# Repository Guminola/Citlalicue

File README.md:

# Citlalicue
Repositories of the Citlallicue mission

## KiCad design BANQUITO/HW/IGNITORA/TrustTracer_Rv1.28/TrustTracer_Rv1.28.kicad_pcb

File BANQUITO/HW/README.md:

# HARDWARE DE BANQUITO

Investigación y desarrollo de hardware para el banco de pruebas

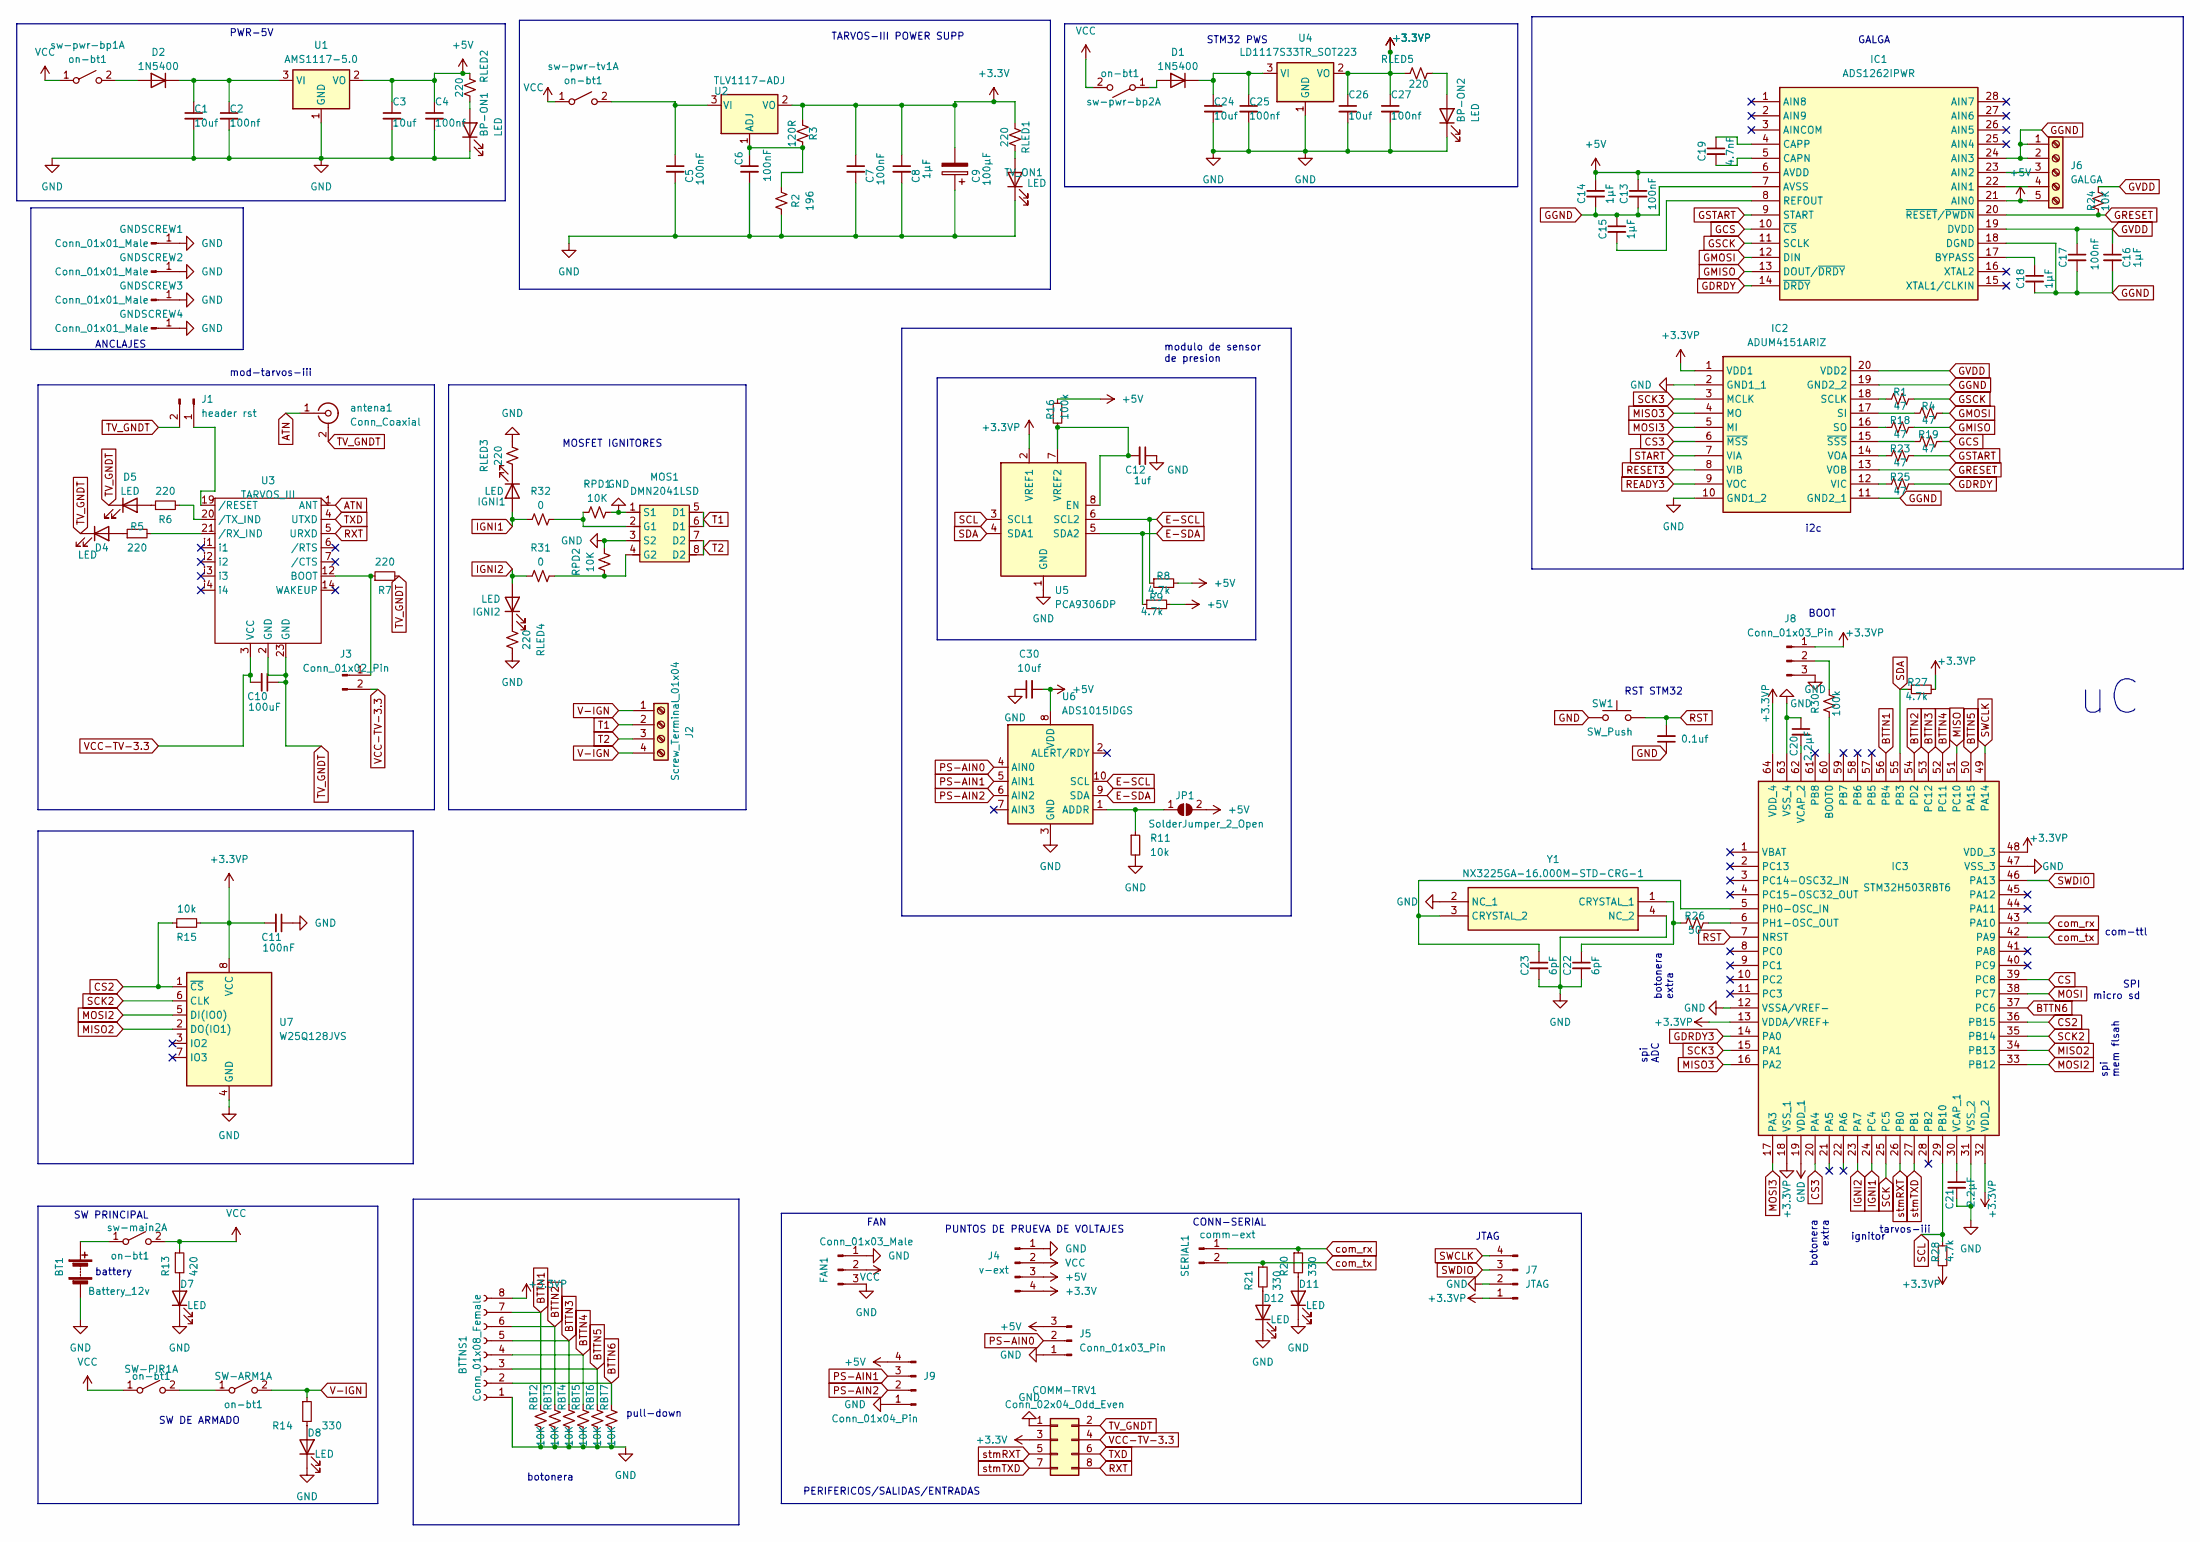
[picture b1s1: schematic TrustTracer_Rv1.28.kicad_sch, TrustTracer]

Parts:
BP-ON1, BP-ON2: LED; LED_0805_2012Metric
BT1: Battery_12v; AMASS_XT30UPB-M_1x02_P5.0mm_Vertical
BTTNS1: Conn_01x08_Female; JST_EH_B8B-EH-A_1x08_P2.50mm_Vertical
C1, C3, C24, C26, C30: 10uf; C_0805_2012Metric_Pad1.18x1.45mm_HandSolder
C2, C4, C25, C27: 100nf; C_0805_2012Metric_Pad1.18x1.45mm_HandSolder
C5, C6, C7, C11, C13, C17: 100nF; C_0805_2012Metric_Pad1.18x1.45mm_HandSolder
C8, C14, C15, C16, C18: 1μF; C_0805_2012Metric_Pad1.18x1.45mm_HandSolder
C9: 100μF; CP_EIA-2012-12_Kemet-R
C10: 100uF; C_0805_2012Metric_Pad1.18x1.45mm_HandSolder
C12: 1uf; C_0805_2012Metric_Pad1.18x1.45mm_HandSolder
C19: 4.7nF; C_0805_2012Metric_Pad1.18x1.45mm_HandSolder
C20, C21: 2.2μF; C_0805_2012Metric_Pad1.18x1.45mm_HandSolder
C22, C23: 6pF; C_0805_2012Metric_Pad1.18x1.45mm_HandSolder
C28: 0.1uf; C_0805_2012Metric_Pad1.18x1.45mm_HandSolder
COMM-TRV1: Conn_02x04_Odd_Even; PinHeader_2x04_P2.00mm_Vertical
D1, D2: 1N5400; D_SOD-123F
D4, D5, D7, D8, D11, D12: LED; LED_0805_2012Metric
FAN1: Conn_01x03_Male; PinHeader_1x03_P2.54mm_Vertical
GNDSCREW1, GNDSCREW2, GNDSCREW3, GNDSCREW4: Conn_01x01_Male; MountingHole_2.2mm_M2_Pad_Via
IC1: ADS1262IPWR; ADS1263IPWR; Manufacturer_Part_Number ADS1262IPWR; Mouser Part Number 595-ADS1262IPWR
IC2: ADUM4151ARIZ; Manufacturer_Part_Number ADUM4151ARIZ; Mouser Part Number 584-ADUM4151ARIZ
IC3: STM32H503RBT6; Manufacturer_Part_Number STM32H503RBT6
IGNI1, IGNI2: LED; LED_0805_2012Metric
J1: header rst; PinHeader_1x02_P2.54mm_Vertical
J2: Screw_Terminal_01x04; TerminalBlock_Phoenix_PT-1,5-4-5.0-H_1x04_P5.00mm_Horizontal
J3: Conn_01x02_Pin; PinHeader_1x02_P2.54mm_Vertical
J4: v-ext; PinHeader_1x04_P2.54mm_Vertical
J5: Conn_01x03_Pin; TerminalBlock_Phoenix_PT-1,5-3-3.5-H_1x03_P3.50mm_Horizontal
J6: GALGA; TerminalBlock_Phoenix_PT-1,5-5-3.5-H_1x05_P3.50mm_Horizontal
J7: JTAG; PinHeader_1x04_P2.54mm_Vertical
J8: Conn_01x03_Pin; PinHeader_1x03_P2.54mm_Vertical
J9: Conn_01x04_Pin; PinHeader_1x04_P2.54mm_Vertical
JP1: SolderJumper_2_Open; SolderJumper-2_P1.3mm_Open_RoundedPad1.0x1.5mm
MOS1: DMN2041LSD; SOIC127P600X175-8M
R1, R4, R18, R19, R23, R25: 47; R_0805_2012Metric_Pad1.20x1.40mm_HandSolder
R2: 196; R_0805_2012Metric_Pad1.20x1.40mm_HandSolder
R3: 120R; R_0805_2012Metric_Pad1.20x1.40mm_HandSolder
R5, R6, R7: 220; R_0805_2012Metric_Pad1.20x1.40mm_HandSolder
R8, R9, R27, R28: 4.7k; R_0805_2012Metric_Pad1.20x1.40mm_HandSolder
R11, R15: 10k; R_0805_2012Metric_Pad1.20x1.40mm_HandSolder
R13: 420; R_0805_2012Metric_Pad1.20x1.40mm_HandSolder
R14, R20, R21: 330; R_0805_2012Metric_Pad1.20x1.40mm_HandSolder
R16, R30: 100k; R_0805_2012Metric_Pad1.20x1.40mm_HandSolder
R24: 10K; R_0805_2012Metric_Pad1.20x1.40mm_HandSolder
R26: 50; R_0805_2012Metric_Pad1.20x1.40mm_HandSolder
R31, R32: 0; R_0805_2012Metric_Pad1.20x1.40mm_HandSolder
RBT2, RBT3, RBT4, RBT5, RBT6, RBT7: 10K; R_0805_2012Metric_Pad1.20x1.40mm_HandSolder
RLED1, RLED2, RLED3, RLED4, RLED5: 220; R_0805_2012Metric_Pad1.20x1.40mm_HandSolder
RPD1, RPD2: 10K; R_0805_2012Metric_Pad1.20x1.40mm_HandSolder
SERIAL1: comm-ext; PinHeader_1x02_P2.54mm_Vertical
SW1: SW_Push; SW_SPST_TL3342
SW-ARM1: on-bt1; TerminalBlock_Phoenix_PT-1,5-2-3.5-H_1x02_P3.50mm_Horizontal
SW-PIR1: on-bt1; TerminalBlock_Phoenix_PT-1,5-2-3.5-H_1x02_P3.50mm_Horizontal
TV_ON1: LED; LED_0805_2012Metric
U1: AMS1117-5.0; SOT-223-3_TabPin2
U2: TLV1117-ADJ; SOT-223
U3: TARVOS_III; tarvos-iii
U4: LD1117S33TR_SOT223; SOT-223-3_TabPin2
U5: PCA9306DP; TSSOP-8_3x3mm_P0.65mm
U6: ADS1015IDGS; TSSOP-10_3x3mm_P0.5mm
U7: W25Q128JVS; SOIC127P600X175-8M
Y1: NX3225GA-16.000M-STD-CRG-1; NX3225GA16000MSTDCRG1; Mouser Part Number 344-NX3225GA16MSTRG1
antena1: Conn_Coaxial; SMA_Wurth_60312002114503_Vertical
sw-main2: on-bt1; TerminalBlock_Phoenix_PT-1,5-2-3.5-H_1x02_P3.50mm_Horizontal
sw-pwr-bp1, sw-pwr-bp2: on-bt1; TerminalBlock_Phoenix_PT-1,5-2-3.5-H_1x02_P3.50mm_Horizontal
sw-pwr-tv1: on-bt1; TerminalBlock_Phoenix_PT-1,5-2-3.5-H_1x02_P3.50mm_Horizontal

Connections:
+3.3V: C7.1, C8.1, C9.2, COMM-TRV1.3, J4.4, R3.2, RLED1.2, U2.2 (VO)
+3.3VP: BTTNS1.8, C11.2, C26.1, C27.1, IC2.1 (VDD1), IC3.13 (VDDA/VREF+), IC3.19 (VDD_1), IC3.32 (VDD_2), IC3.48 (VDD_3), IC3.64 (VDD_4), J7.1, J8.1, R15.2, R27.2, R28.2, RLED5.2, U4.2 (VO), U5.2 (VREF1), U7.8 (VCC)
+5V: C3.1, C4.1, C13.1, C14.1, C30.2, IC1.6 (AVDD), IC1.21 (AIN0), J4.3, J5.3, J6.5, J9.4, JP1.2 (B), R8.2, R9.2, R16.1, RLED2.2, U1.2 (VO), U6.8 (VDD)
ATN: U3.1 (ANT), antena1.1 (In)
BTTN1: BTTNS1.7, IC3.56 (PB4), RBT2.1
BTTN2: BTTNS1.6, IC3.54 (PD2), RBT3.1
BTTN3: BTTNS1.5, IC3.53 (PC12), RBT4.1
BTTN4: BTTNS1.4, IC3.52 (PC11), RBT5.1
BTTN5: BTTNS1.3, IC3.50 (PA15), RBT6.1
BTTN6: BTTNS1.2, IC3.37 (PC6), RBT7.1
CS: IC3.39 (PC8)
CS2: IC3.36 (PB15), R15.1, U7.1 (~CS)
CS3: IC2.6 (~MSS), IC3.20 (PA4)
E-SCL: R8.1, U5.6 (SCL2), U6.10 (SCL)
E-SDA: R9.1, U5.5 (SDA2), U6.9 (SDA)
GCS: IC1.10 (~CS), R19.2
GDRDY: IC1.14 (~DRDY), R25.2
GDRDY3: IC3.14 (PA0)
GGND: C13.2, C14.2, C15.1, C16.2, C17.2, C18.2, IC1.7 (AVSS), IC1.18 (DGND), IC1.24 (AIN3), IC2.11 (GND2_1), IC2.19 (GND2_2), J6.1, J6.2
GMISO: IC1.13 (DOUT/~DRDY), R18.2
GMOSI: IC1.12 (DIN), R4.2
GND: BP-ON1.1 (K), BP-ON2.1 (K), BT1.2 (-), BTTNS1.1, C1.2, C2.2, C3.2, C4.2, C5.2, C6.2, C7.2, C8.2, C9.1, C11.1, C12.1, C20.1, C21.2, C22.2, C23.2, C24.2, C25.2, C26.2, C27.2, C28.1, C30.1, COMM-TRV1.1, D7.1 (K), D8.1 (K), D11.1 (K), D12.1 (K), FAN1.1, FAN1.3, GNDSCREW1.1, GNDSCREW2.1, GNDSCREW3.1, GNDSCREW4.1, IC2.2 (GND1_1), IC2.10 (GND1_2), IC3.12 (VSSA/VREF-), IC3.18 (VSS_1), IC3.31 (VSS_2), IC3.47 (VSS_3), IC3.63 (VSS_4), J4.1, J5.1, J7.2, J8.3, J9.1, MOS1.1 (S1), MOS1.3 (S2), R2.1, R11.2, RBT2.2, RBT3.2, RBT4.2, RBT5.2, RBT6.2, RBT7.2, RLED3.2, RLED4.2, RPD1.2, RPD2.2, SW1.1, TV_ON1.1 (K), U1.1 (GND), U4.1 (GND), U5.1 (GND), U6.3 (GND), U7.4 (GND), Y1.2 (NC_1), Y1.4 (NC_2)
GRESET: IC1.20 (~RESET/~PWDN), IC2.13 (VOB), R24.1
GSCK: IC1.11 (SCLK), R1.2
GSTART: IC1.9 (START), R23.2
GVDD: C16.1, C17.1, IC1.19 (DVDD), IC2.20 (VDD2), R24.2
IGNI1: IC3.24 (PC4), IGNI1.2 (A), R32.1
IGNI2: IC3.23 (PA7), IGNI2.2 (A), R31.1
MISO: IC3.51 (PC10)
MISO2: IC3.34 (PB13), U7.2 (DO(IO1))
MISO3: IC2.4 (MO), IC3.16 (PA2)
MOSI: IC3.38 (PC7)
MOSI2: IC3.33 (PB12), U7.5 (DI(IO0))
MOSI3: IC2.5 (MI), IC3.17 (PA3)
unnamed: BP-ON1.2 (A), RLED2.1
unnamed: BP-ON2.2 (A), RLED5.1
unnamed: BT1.1 (+), sw-main2.1 (A)
unnamed: D1.2 (A), sw-pwr-bp2.1 (A)
unnamed: C24.1, C25.1, D1.1 (K), U4.3 (VI)
unnamed: D2.2 (A), sw-pwr-bp1.2 (B)
unnamed: C1.1, C2.1, D2.1 (K), U1.3 (VI)
unnamed: D4.2 (A), R5.1
unnamed: D5.2 (A), R6.1
unnamed: D7.2 (A), R13.2
unnamed: D8.2 (A), R14.2
unnamed: D11.2 (A), R20.2
unnamed: D12.2 (A), R21.2
unnamed: IC1.22 (AIN1), J6.4
unnamed: IC1.23 (AIN2), J6.3
unnamed: C18.1, IC1.17 (BYPASS)
unnamed: C19.2, IC1.5 (CAPN)
unnamed: C19.1, IC1.4 (CAPP)
unnamed: C15.2, IC1.8 (REFOUT)
unnamed: IC2.18 (SCLK), R1.1
unnamed: IC2.17 (SI), R4.1
unnamed: IC2.16 (SO), R18.1
unnamed: IC2.12 (VIC), R25.1
unnamed: IC2.14 (VOA), R23.1
unnamed: IC2.15 (~SSS), R19.1
unnamed: IC3.60 (BOOT0), R30.1
unnamed: C23.1, IC3.5 (PH0-OSC_IN), Y1.3 (CRYSTAL_2)
unnamed: IC3.6 (PH1-OSC_OUT), R26.2
unnamed: C21.1, IC3.30 (VCAP_1)
unnamed: C20.2, IC3.62 (VCAP_2)
unnamed: IGNI1.1 (K), RLED3.1
unnamed: IGNI2.1 (K), RLED4.1
unnamed: J1.1, U3.19 (/RESET)
unnamed: J3.1, R7.1, U3.12 (BOOT)
unnamed: J8.2, R30.2
unnamed: JP1.1 (A), R11.1, U6.1 (ADDR)
unnamed: MOS1.2 (G1), R32.2, RPD1.1
unnamed: MOS1.4 (G2), R31.2, RPD2.1
unnamed: SW-ARM1.1 (A), SW-PIR1.2 (B)
unnamed: RLED1.1, TV_ON1.2 (A)
unnamed: C6.1, R2.2, R3.1, U2.1 (ADJ)
unnamed: C5.1, U2.3 (VI), sw-pwr-tv1.2 (B)
unnamed: R5.2, U3.21 (/RX_IND)
unnamed: R6.2, U3.20 (/TX_IND)
unnamed: C12.2, R16.2, U5.7 (VREF2), U5.8 (EN)
unnamed: C22.1, R26.1, Y1.1 (CRYSTAL_1)
PS-AIN0: J5.2, U6.4 (AIN0)
PS-AIN1: J9.3, U6.5 (AIN1)
PS-AIN2: J9.2, U6.6 (AIN2)
READY3: IC2.9 (VOC)
RESET3: IC2.8 (VIB)
RST: C28.2, IC3.7 (NRST), SW1.2
RXT: COMM-TRV1.8, U3.5 (URXD)
SCK: IC3.25 (PC5)
SCK2: IC3.35 (PB14), U7.6 (CLK)
SCK3: IC2.3 (MCLK), IC3.15 (PA1)
SCL: IC3.29 (PB10), R28.1, U5.3 (SCL1)
SDA: IC3.55 (PB3), R27.1, U5.4 (SDA1)
START: IC2.7 (VIA)
SWCLK: IC3.49 (PA14), J7.4
SWDIO: IC3.46 (PA13), J7.3
T1: J2.2, MOS1.5 (D1), MOS1.6 (D1)
T2: J2.3, MOS1.7 (D2), MOS1.8 (D2)
TV_GNDT: C10.1, COMM-TRV1.2, D4.1 (K), D5.1 (K), J1.2, R7.2, U3.2 (GND), U3.23 (GND), antena1.2 (Ext)
TXD: COMM-TRV1.6, U3.4 (UTXD)
V-IGN: J2.1, J2.4, R14.1, SW-ARM1.2 (B)
VCC: FAN1.2, J4.2, R13.1, SW-PIR1.1 (A), sw-main2.2 (B), sw-pwr-bp1.1 (A), sw-pwr-bp2.2 (B), sw-pwr-tv1.1 (A)
VCC-TV-3.3: C10.2, COMM-TRV1.4, J3.2, U3.3 (VCC)
com_rx: IC3.43 (PA10), R20.1, SERIAL1.1
com_tx: IC3.42 (PA9), R21.1, SERIAL1.2
stmRXT: COMM-TRV1.5, IC3.26 (PB0)
stmTXD: COMM-TRV1.7, IC3.27 (PB1)

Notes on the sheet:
JTAG
ignitor
PERIFERICOS/SALIDAS/ENTRADAS
mod-tarvos-iii
PUNTOS DE PRUEVA DE VOLTAJES
battery
BOOT
ANCLAJES
botonera
TARVOS-III POWER SUPP
FAN
SW PRINCIPAL
spi ADC
SW DE ARMADO
botonera extra
PWR-5V
GALGA
i2c
com-ttl
pull-down
tarvos-iii
MOSFET IGNITORES
STM32 PWS
SPI micro sd
modulo de sensor de presion
CONN-SERIAL
RST STM32
spi mem flsah

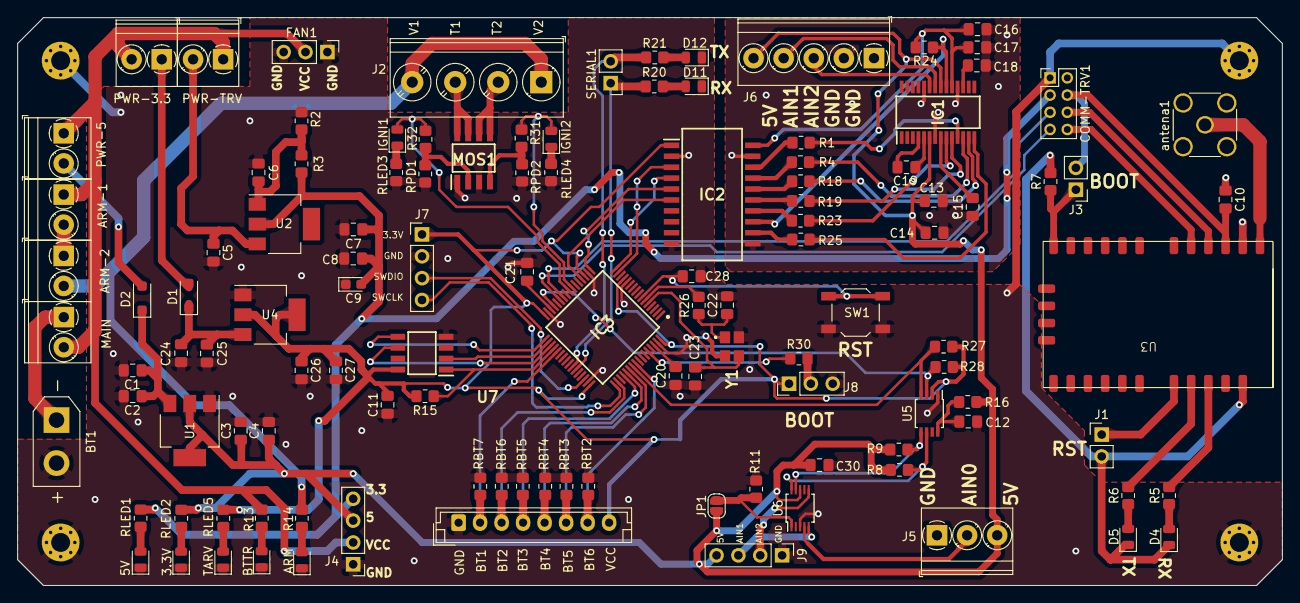
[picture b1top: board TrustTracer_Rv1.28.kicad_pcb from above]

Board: 2 copper layers, 147.0 x 66.0 mm, 122 parts (1 on the bottom side), 98 nets.

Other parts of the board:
G2: LOGO; SPACE

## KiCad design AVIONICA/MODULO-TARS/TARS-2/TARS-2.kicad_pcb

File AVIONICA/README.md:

# AVIONICA PARA LA MISION

T.A.R.S

Telemetry, Avionics,Recovery,System

sistema de avionica y sus diferentes modulos de la mision

1/3 modulo gps  Erinome-1

2/3 modulo de comunicaciones Tarvos-iii

3/3 avionica STM-32

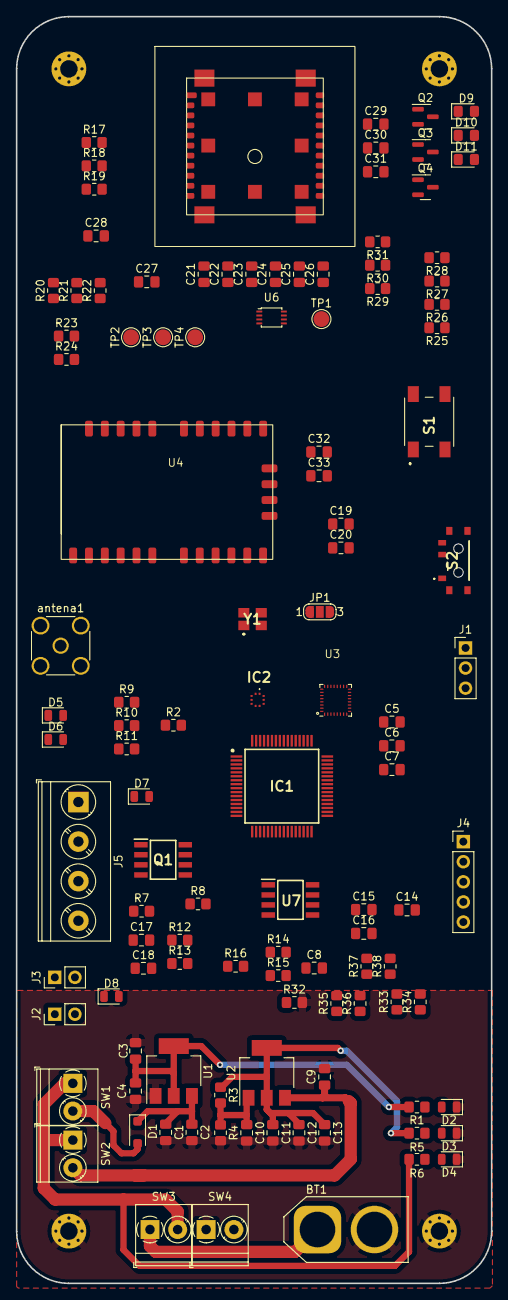
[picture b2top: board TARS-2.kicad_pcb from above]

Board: 2 copper layers, 60.0 x 160.0 mm, 118 parts (0 on the bottom side), 70 nets.

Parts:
BT1: Battery; AMASS_XT60-M_1x02_P7.20mm_Vertical
C1, C3: 10uf; C_0805_2012Metric_Pad1.18x1.45mm_HandSolder
C2, C4, C9, C10, C11, C18, C19, C27, C28: 100nf; C_0805_2012Metric_Pad1.18x1.45mm_HandSolder
C5, C6, C7, C8: 6pf; C_0805_2012Metric_Pad1.18x1.45mm_HandSolder
C12, C32: 1uf; C_0805_2012Metric_Pad1.18x1.45mm_HandSolder
C13: 100uf; C_0805_2012Metric_Pad1.18x1.45mm_HandSolder
C14: C_Small; C_0805_2012Metric_Pad1.18x1.45mm_HandSolder
C15: .1uf; C_0805_2012Metric_Pad1.18x1.45mm_HandSolder
C16, C17: .1f; C_0805_2012Metric_Pad1.18x1.45mm_HandSolder
C20: 100uF; C_0805_2012Metric_Pad1.18x1.45mm_HandSolder
C21, C23, C29, C30, C31: 100pf; C_0805_2012Metric_Pad1.18x1.45mm_HandSolder
C22, C24: 4.7uf; C_0805_2012Metric_Pad1.18x1.45mm_HandSolder
C25, C26: 18pf; C_0805_2012Metric_Pad1.18x1.45mm_HandSolder
C33: 100nF; C_0805_2012Metric_Pad1.18x1.45mm_HandSolder
D1: 1N5400; D_SOD-123F
D2, D7, D8: LED; LED_0805_2012Metric
D3, D4, D5, D6: LED_Small; LED_0805_2012Metric
D9, D10, D11: LED_Small; LED_0805_2012Metric_Pad1.15x1.40mm_HandSolder
GNDSCREW1, GNDSCREW2, GNDSCREW3, GNDSCREW4: Conn_01x01_Male; MountingHole_2.2mm_M2_Pad_Via
IC1: STM32H503RBT6
IC2: BMP390
J1: Conn_01x03_Pin; PinHeader_1x03_P2.54mm_Vertical
J2: header rst; PinHeader_1x02_P2.54mm_Vertical
J3: Conn_01x02_Pin; PinHeader_1x02_P2.54mm_Vertical
J4: Conn_01x05_Pin; PinHeader_1x05_P2.54mm_Vertical
J5: Screw_Terminal_01x04; TerminalBlock_Phoenix_PT-1,5-4-5.0-H_1x04_P5.00mm_Horizontal
JP1: Jumper_3_Open; SolderJumper-3_P1.3mm_Open_RoundedPad1.0x1.5mm_NumberLabels
Q1: DMN2041LSD-13; SOIC127P600X175-8M
Q2, Q3, Q4: BSS138; SOT-23
R1, R5, R12, R13, R14, R15, R16: 220; R_0805_2012Metric_Pad1.20x1.40mm_HandSolder
R2: 50; R_0805_2012Metric_Pad1.20x1.40mm_HandSolder
R3: 120; R_0805_2012Metric_Pad1.20x1.40mm_HandSolder
R4: 196; R_0805_2012Metric_Pad1.20x1.40mm_HandSolder
R6: 420; R_0805_2012Metric_Pad1.20x1.40mm_HandSolder
R7, R24, R28, R29: 100k; R_0805_2012Metric_Pad1.20x1.40mm_HandSolder
R8, R9, R19, R23, R26, R27, R32, R33, R38: 10k; R_0805_2012Metric_Pad1.20x1.40mm_HandSolder
R10, R11, R20: 0; R_0805_2012Metric_Pad1.20x1.40mm_HandSolder
R17, R18: 100; R_0805_2012Metric_Pad1.20x1.40mm_HandSolder
R21: 1.8k; R_0805_2012Metric_Pad1.20x1.40mm_HandSolder
R22: 1.5k; R_0805_2012Metric_Pad1.20x1.40mm_HandSolder
R25, R31: 2.2k; R_0805_2012Metric_Pad1.20x1.40mm_HandSolder
R30: 1k; R_0805_2012Metric_Pad1.20x1.40mm_HandSolder
R34, R35, R36, R37: 330; R_0805_2012Metric_Pad1.20x1.40mm_HandSolder
S1: PSB-WURT
S2: SW-WURT
SW1, SW3: MAIN; TerminalBlock_Phoenix_PT-1,5-2-3.5-H_1x02_P3.50mm_Horizontal
SW2: TRV-PWR; TerminalBlock_Phoenix_PT-1,5-2-3.5-H_1x02_P3.50mm_Horizontal
SW4: RST; TerminalBlock_Phoenix_PT-1,5-2-3.5-H_1x02_P3.50mm_Horizontal
TP1: CTS; TestPoint_Pad_D2.0mm
TP2: GND; TestPoint_Pad_D2.0mm
TP3: 1v8; TestPoint_Pad_D2.0mm
TP4: RTS; TestPoint_Pad_D2.0mm
U1: LD1117S33TR_SOT223; SOT-223-3_TabPin2
U2: TLV1117-ADJ; SOT-223-3_TabPin2
U3: ICM-30670
U4: TARVOS_III; tarvos-iii
U5: ERINOME-l; Erinome-l
U6: TXB0102DCU; VSSOP-8_2.4x2.1mm_P0.5mm
U7: W25Q128JVS; SOIC127P600X175-8M
Y1: NX3225GA-16.000M-STD-CRG-1; NX3225GA16000MSTDCRG1
antena1: Conn_Coaxial; SMA_Wurth_60312002114503_Vertical

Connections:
1pps: R26.1, U5.21 (1PPS)
3v3-ldo: C23.1, C24.1, U5.3 (V_BACKUP)
+1V8: R20.1, TP3.1, U5.9 (1V8)
+3.3V: C11.1, C12.1, C13.1, C21.1, C22.1, C28.1, D9.2 (A), D10.2 (A), D11.2 (A), R3.1, R5.1, R19.2, R22.2, S2.1, U2.2 (VO), U5.8 (VCC), U6.7 (VCCB)
+12V: R6.1, SW1.1 (A), SW2.1 (A), SW3.2 (B)
ATN: U4.1 (ANT), antena1.1 (In)
CS2: R38.1, U7.1 (~CS)
GND: BT1.2 (-), C1.2, C2.2, C3.2, C4.2, C5.2, C6.2, C7.1, C8.2, C9.2, C10.2, C11.2, C12.2, C13.2, C14.2, C15.1, C16.1, C17.1, C18.2, C19.2, C21.2, C22.2, C23.2, C24.2, C25.1, C26.1, C27.2, C28.2, C29.2, C30.2, C31.2, C32.2, C33.1, D2.1 (K), D3.1 (K), D4.1 (K), GNDSCREW1.1, GNDSCREW2.1, GNDSCREW3.1, GNDSCREW4.1, IC1.12 (VSSA/VREF-), IC1.18 (VSS_1), IC1.31 (VSS_2), IC1.47 (VSS_3), IC1.63 (VSS_4), IC2.3 (VSS_1), IC2.8 (VSS_2), IC2.9 (VSS_3), J1.3, J4.5, JP1.1 (A), Q1.1 (S1), Q1.3 (S2), Q2.2 (S), Q3.2 (S), Q4.2 (S), R4.2, R8.2, R9.2, R12.1, R13.2, R21.2, R24.2, R28.2, R29.2, R32.2, S2.3, SW4.1, TP2.1, U1.1 (GND), U3.1 (VDDIO), U3.14 (GND), U5.10 (GND), U5.11 (GND), U5.12 (GND), U6.2 (GND), U7.4 (GND), Y1.2 (NC_1), Y1.4 (NC_2)
IGN1: D5.2 (A), R10.1
IGN2: D6.2 (A), R11.1
unnamed: BT1.1 (+), SW3.1 (A)
unnamed: D1.2 (A), SW1.2 (B)
unnamed: C1.1, C2.1, D1.1 (K), U1.3 (VI)
unnamed: D2.2 (A), R1.1
unnamed: D3.2 (A), R5.2
unnamed: D4.2 (A), R6.2
unnamed: D5.1 (K), R12.2
unnamed: D6.1 (K), R13.1
unnamed: D7.2 (A), R14.1
unnamed: D8.2 (A), R15.1
unnamed: D9.1 (K), R25.1
unnamed: D10.1 (K), R30.1
unnamed: D11.1 (K), R31.1
unnamed: IC1.60 (BOOT0), R7.2
unnamed: C5.1, IC1.5 (PH0-OSC_IN), Y1.3 (CRYSTAL_2)
unnamed: IC1.6 (PH1-OSC_OUT), R2.2
unnamed: C8.1, IC1.30 (VCAP_1)
unnamed: C7.2, IC1.62 (VCAP_2)
unnamed: IC2.5 (SDO), JP1.2 (C)
unnamed: J1.2, R7.1
unnamed: J2.1, U4.19 (/RESET)
unnamed: J3.1, R16.1, U4.12 (BOOT)
unnamed: J4.1, R34.2
unnamed: J4.2, R35.2
unnamed: J4.3, R36.2
unnamed: J4.4, R37.2
unnamed: Q1.2 (G1), R8.1, R10.2
unnamed: Q1.4 (G2), R9.1, R11.2
unnamed: Q2.3 (D), R25.2
unnamed: C29.1, Q2.1 (G), R23.2, R24.1
unnamed: Q3.3 (D), R30.2
unnamed: C30.1, Q3.1 (G), R26.2, R28.1
unnamed: Q4.3 (D), R31.2
unnamed: C31.1, Q4.1 (G), R27.2, R29.1
unnamed: R33.1, S2.2
unnamed: R32.1, S1.1 (NO_1), S1.2 (NO_2)
unnamed: C9.1, SW2.2 (B), U2.3 (VI)
unnamed: C10.1, R3.2, R4.1, U2.1 (ADJ)
unnamed: C16.2, U3.11 (REGOUT)
unnamed: R14.2, U4.21 (/RX_IND)
unnamed: R15.2, U4.20 (/TX_IND)
unnamed: C25.2, R17.2, U5.1 (RX)
unnamed: C26.2, R18.2, U5.2 (TX)
unnamed: TP1.1, U5.4 (/CTS)
unnamed: TP4.1, U6.8 (B1)
unnamed: C6.1, R2.1, Y1.1 (CRYSTAL_1)
ON-OFF: R33.2, U5.17 (ON_OF)
RST: C14.1, C32.1, S1.3 (COM_1), S1.4 (COM_2), SW4.2, U5.16 (/RST)
RTS-1V8: U5.5 (/RTS), U6.5 (A1)
SCL: IC2.2 (SCK), U3.10 (SCLK/SCL)
SDA: IC2.4 (SDI), U3.9 (SDI/SDA)
T1: J5.2, Q1.7 (D1_1), Q1.8 (D1_2)
T2: J5.3, Q1.5 (D2_1), Q1.6 (D2_2)
TV_GNDT: C20.1, D7.1 (K), D8.1 (K), J2.2, R16.2, U4.2 (GND), U4.23 (GND), antena1.2 (Ext)
TX-GNSS-1V8: R18.1, R27.1, U6.4 (A2)
V-IGN: J5.1, J5.4
VCC-TV-3.3: C20.2, J3.2, U4.3 (VCC)
VCCA: C27.1, R20.2, R21.1, R22.1, U6.3 (VCCA), U6.6 (OE)
VDDIO: C3.1, C4.1, C15.2, C17.2, C18.1, C19.1, C33.2, IC1.13 (VDDA/VREF+), IC1.19 (VDD_1), IC1.32 (VDD_2), IC1.48 (VDD_3), IC1.64 (VDD_4), IC2.1 (VDDIO), IC2.10 (VDD), J1.1, JP1.3 (B), R1.2, R38.2, U1.2 (VO), U3.12 (VDD), U7.8 (VCC)
wkp: R23.1, U5.15 (WAKE-UP)

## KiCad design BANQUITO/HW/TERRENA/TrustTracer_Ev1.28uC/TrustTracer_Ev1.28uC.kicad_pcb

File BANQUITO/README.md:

# Banco-de-Pruebas

Investigación y desarrollo de hardware y software para el banco de pruebas

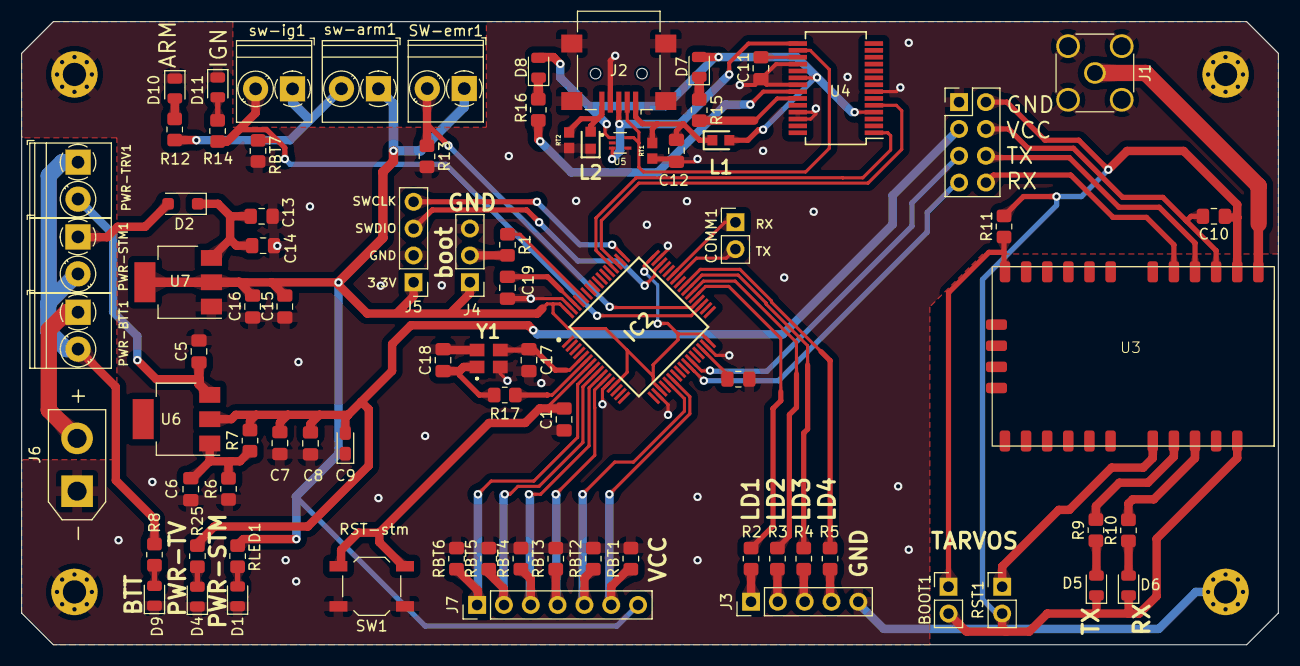
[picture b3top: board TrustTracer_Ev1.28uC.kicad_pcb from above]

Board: 2 copper layers, 119.0 x 59.0 mm, 87 parts (1 on the bottom side), 68 nets.

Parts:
BOOT1: Conn_01x02_Pin; PinHeader_1x02_P2.54mm_Vertical
C1: 0.1uf; C_0805_2012Metric_Pad1.18x1.45mm_HandSolder
C5, C6, C7, C11: 100nF; C_0805_2012Metric_Pad1.18x1.45mm_HandSolder
C8: 1μF; C_0805_2012Metric_Pad1.18x1.45mm_HandSolder
C9: 100μF; CP_EIA-2012-15_AVX-P_Pad1.30x1.05mm_HandSolder
C10: 100uF; C_0805_2012Metric_Pad1.18x1.45mm_HandSolder
C12: 10nF; C_0805_2012Metric_Pad1.18x1.45mm_HandSolder
C13, C15: 10uf; C_0805_2012Metric_Pad1.18x1.45mm_HandSolder
C14, C16: 100nf; C_0805_2012Metric_Pad1.18x1.45mm_HandSolder
C17, C18: 6pF; C_0805_2012Metric_Pad1.18x1.45mm_HandSolder
C19, C20: 2.2μF; C_0805_2012Metric_Pad1.18x1.45mm_HandSolder
COMM1: comm-ext; PinHeader_1x02_P2.54mm_Vertical
COMM-TRV1: Conn_02x04_Odd_Even; PinHeader_2x04_P2.54mm_Vertical
D1, D4, D5, D6, D7, D8, D9, D10, D11: LED; LED_0805_2012Metric
D2: 1N5400; D_SOD-123F
G2: LOGO; SPACE
GNDSCREW1, GNDSCREW2, GNDSCREW3, GNDSCREW4: Conn_01x01_Male; MountingHole_2.2mm_M2_Pad_Via
IC2: STM32H503RBT6
J1: Conn_Coaxial; SMA_Wurth_60312002114503_Vertical
J2: USB_B_Micro; USB_Mini-B_Lumberg_2486_01_Horizontal
J3: Conn_01x05_Pin; PinHeader_1x05_P2.54mm_Vertical
J4: Conn_01x03_Pin; PinHeader_1x03_P2.54mm_Vertical
J5: JTAG; PinHeader_1x04_P2.54mm_Vertical
J6: batt-conn; AMASS_XT30UPB-M_1x02_P5.0mm_Vertical
J7: Conn_01x07_Socket; PinHeader_1x07_P2.54mm_Vertical
L1, L2: 74279263; 220-100mhz-500mha
PWR-BTT1: on-bt1; TerminalBlock_Phoenix_PT-1,5-2-3.5-H_1x02_P3.50mm_Horizontal
PWR-STM1: on-bt1; TerminalBlock_Phoenix_PT-1,5-2-3.5-H_1x02_P3.50mm_Horizontal
PWR-TRV1: SW_DPST_x2; TerminalBlock_Phoenix_PT-1,5-2-3.5-H_1x02_P3.50mm_Horizontal
R1: 100k; R_0805_2012Metric_Pad1.20x1.40mm_HandSolder
R2, R3, R4, R5, R8, R12, R14: 330; R_0805_2012Metric_Pad1.20x1.40mm_HandSolder
R6: 196; R_0805_2012Metric_Pad1.20x1.40mm_HandSolder
R7: 120R; R_0805_2012Metric_Pad1.20x1.40mm_HandSolder
R9, R10, R11, R25: 220; R_0805_2012Metric_Pad1.20x1.40mm_HandSolder
R13: 10k; R_0805_2012Metric_Pad1.20x1.40mm_HandSolder
R15, R16: 270; R_0805_2012Metric_Pad1.20x1.40mm_HandSolder
R17: 50; R_0805_2012Metric_Pad1.20x1.40mm_HandSolder
RBT1, RBT2, RBT3, RBT4, RBT5, RBT6, RBT7: 10K; R_0805_2012Metric_Pad1.20x1.40mm_HandSolder
RLED1: 220; R_0805_2012Metric_Pad1.20x1.40mm_HandSolder
RST1: header rst; PinHeader_1x02_P2.54mm_Vertical
RT1, RT2: NCP18XM472E03RB; THRMC1608X95N
SW1: SW_Push; SW_SPST_TL3342
SW-emr1: SW_Push_Open; TerminalBlock_Phoenix_PT-1,5-2-3.5-H_1x02_P3.50mm_Horizontal
U3: TARVOS_III; tarvos-iii
U4: FT232RL; SSOP-28_5.3x10.2mm_P0.65mm
U5: TPD2E001DRLR; SOT50P160X60-5N
U6: TLV1117-ADJ; SOT-223
U7: LD1117S33TR_SOT223; SOT-223-3_TabPin2
Y1: NX3225GA-16.000M-STD-CRG-1; NX3225GA16000MSTDCRG1
sw-arm1: armado; TerminalBlock_Phoenix_PT-1,5-2-3.5-H_1x02_P3.50mm_Horizontal
sw-ig1: ignicion; TerminalBlock_Phoenix_PT-1,5-2-3.5-H_1x02_P3.50mm_Horizontal

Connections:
12V: PWR-BTT1.2 (B), PWR-STM1.2 (B), PWR-TRV1.1 (A), R8.1
+3.3VP: C15.1, C16.1, IC2.13 (VDDA/VREF+), IC2.19 (VDD_1), IC2.32 (VDD_2), IC2.48 (VDD_3), IC2.64 (VDD_4), J4.1, J5.1, J7.7, RLED1.2, SW-emr1.1 (A), U7.2 (VO), sw-arm1.1 (A)
ANT: J1.1 (In), U3.1 (ANT)
BTTN1: IC2.8 (PC0), J7.1, RBT6.1
BTTN2: IC2.9 (PC1), J7.2, RBT5.1
BTTN3: IC2.10 (PC2), J7.3, RBT4.1
BTTN4: IC2.11 (PC3), J7.4, RBT3.1
BTTN5: IC2.21 (PA5), J7.5, RBT2.1
BTTN6: IC2.22 (PA6), J7.6, RBT1.1
GND: C1.1, C5.2, C6.2, C7.2, C8.2, C9.1, C11.2, C12.1, C13.2, C14.2, C15.2, C16.2, C17.2, C18.2, C19.1, C20.2, COMM-TRV1.1, D1.1 (K), D4.1 (K), D9.1 (K), D10.1 (K), D11.1 (K), GNDSCREW1.1, GNDSCREW2.1, GNDSCREW3.1, GNDSCREW4.1, IC2.12 (VSSA/VREF-), IC2.18 (VSS_1), IC2.31 (VSS_2), IC2.47 (VSS_3), IC2.63 (VSS_4), J1.2 (Ext), J2.4 (ID), J2.6 (Shield), J3.5, J4.3, J5.2, J6.1, L2.1 (K), R6.1, R13.2, RBT1.2, RBT2.2, RBT3.2, RBT4.2, RBT5.2, RBT6.2, RBT7.2, RT1.2, RT2.2, SW1.1, U4.7 (GND), U4.18 (GND), U4.21 (GND), U4.25 (AGND), U4.26 (TEST), U5.4 (GND), U7.1 (GND), Y1.2 (NC_1), Y1.4 (NC_2)
LD1: IC2.37 (PC6), R2.1
LD2: IC2.38 (PC7), R3.1
LD3: IC2.39 (PC8), R4.1
LD4: IC2.40 (PC9), R5.1
unnamed: BOOT1.1, R11.1, U3.12 (BOOT)
unnamed: D1.2 (A), RLED1.1
unnamed: D2.2 (A), PWR-STM1.1 (A)
unnamed: C13.1, C14.1, D2.1 (K), U7.3 (VI)
unnamed: D4.2 (A), R25.1
unnamed: D5.2 (A), R9.1
unnamed: D6.2 (A), R10.1
unnamed: D7.1 (K), R15.1
unnamed: D8.1 (K), R16.1
unnamed: D9.2 (A), R8.2
unnamed: D10.2 (A), R12.2
unnamed: D11.2 (A), R14.2
unnamed: IC2.60 (BOOT0), R1.1
unnamed: C17.1, IC2.5 (PH0-OSC_IN), Y1.3 (CRYSTAL_2)
unnamed: IC2.6 (PH1-OSC_OUT), R17.2
unnamed: C20.1, IC2.30 (VCAP_1)
unnamed: C19.2, IC2.62 (VCAP_2)
unnamed: J2.3 (D+), U4.15 (USBD+), U5.3 (IO1)
unnamed: J2.2 (D-), U4.16 (USBD-), U5.5 (IO2)
unnamed: J2.5 (GND), L2.2 (A), RT2.1
unnamed: C12.2, J2.1 (VBUS), L1.1 (K), RT1.1
unnamed: J3.1, R2.2
unnamed: J3.2, R3.2
unnamed: J3.3, R4.2
unnamed: J3.4, R5.2
unnamed: J4.2, R1.2
unnamed: J6.2, PWR-BTT1.1 (A)
unnamed: C5.1, PWR-TRV1.2 (B), U6.3 (VI)
unnamed: RST1.1, U3.19 (/RESET)
unnamed: R10.2, U3.21 (/RX_IND)
unnamed: R9.2, U3.20 (/TX_IND)
unnamed: C11.1, U4.17 (3V3OUT)
unnamed: R15.2, U4.23 (CBUS0)
unnamed: R16.2, U4.22 (CBUS1)
unnamed: C6.1, R6.2, R7.1, U6.1 (ADJ)
unnamed: C18.1, R17.1, Y1.1 (CRYSTAL_1)
unnamed: R12.1, sw-arm1.2 (B), sw-ig1.1 (A)
RST: C1.2, IC2.7 (NRST), SW1.2
RXT: COMM-TRV1.8, U3.5 (URXD)
ST_RX: IC2.52 (PC11), U4.1 (TXD)
ST_TX: IC2.51 (PC10), U4.5 (RXD)
SWCLK: IC2.49 (PA14), J5.4
SWDIO: IC2.46 (PA13), J5.3
TV_GNDT: BOOT1.2, C10.1, COMM-TRV1.2, D5.1 (K), D6.1 (K), R11.2, RST1.2, U3.2 (GND), U3.23 (GND)
TV_VDD: C7.1, C8.1, C9.2, COMM-TRV1.3, R7.2, R25.2, U6.2 (VO)
TV_VDDT: C10.2, COMM-TRV1.4, U3.3 (VCC)
TXD: COMM-TRV1.6, U3.4 (UTXD)
VUSB: D7.2 (A), D8.2 (A), L1.2 (A), U4.4 (VCCIO), U4.20 (VCC), U5.1 (VCC)
com_rx: COMM1.1, IC2.43 (PA10)
com_tx: COMM1.2, IC2.42 (PA9)
emr: IC2.36 (PB15), R13.1, SW-emr1.2 (B)
stmRXT: COMM-TRV1.7, IC2.26 (PB0)
stmTXD: COMM-TRV1.5, IC2.27 (PB1)
sw-out: IC2.35 (PB14), R14.1, RBT7.1, sw-ig1.2 (B)

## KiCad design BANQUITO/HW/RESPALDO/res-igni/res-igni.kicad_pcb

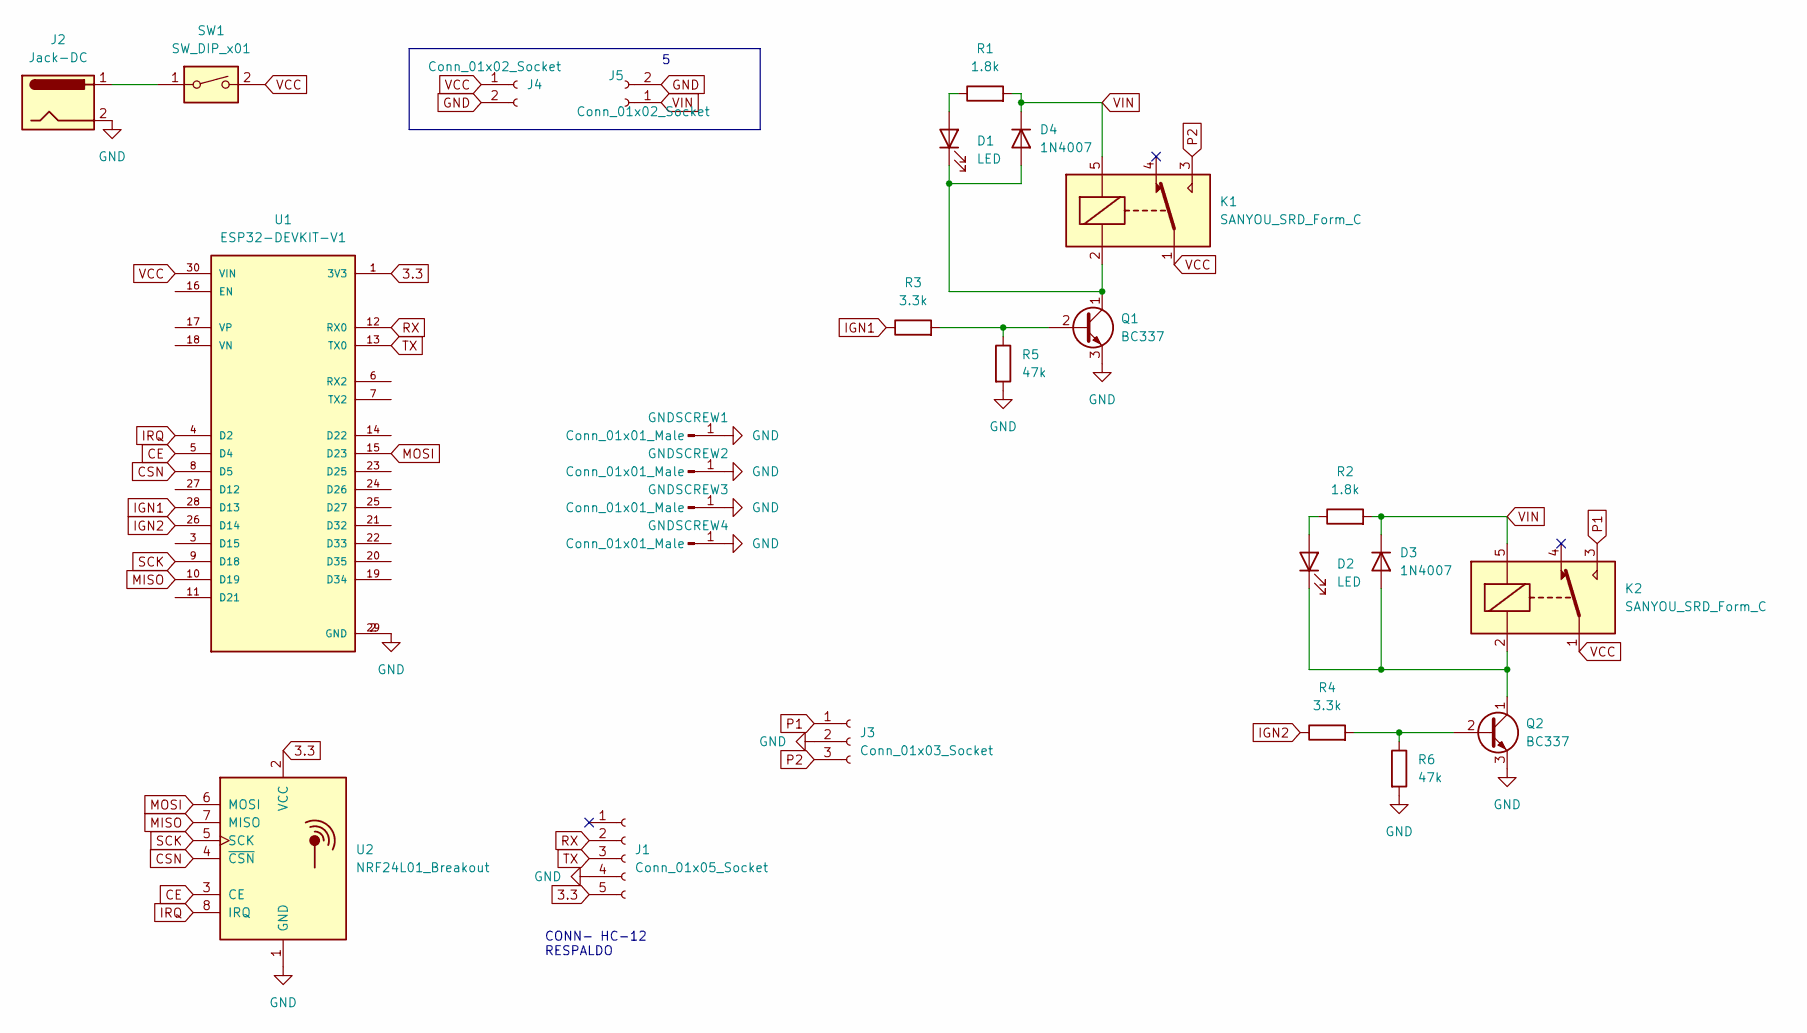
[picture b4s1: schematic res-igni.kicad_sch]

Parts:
D1, D2: LED; LED_D3.0mm
D3, D4: 1N4007; D_DO-41_SOD81_P10.16mm_Horizontal
GNDSCREW1, GNDSCREW2, GNDSCREW3, GNDSCREW4: Conn_01x01_Male; MountingHole_2.2mm_M2_Pad_Via
J1: Conn_01x05_Socket; PinSocket_1x05_P2.54mm_Vertical
J2: Jack-DC; BarrelJack_GCT_DCJ200-10-A_Horizontal
J3: Conn_01x03_Socket; PhoenixContact_MCV_1,5_3-G-5.08_1x03_P5.08mm_Vertical
J4, J5: Conn_01x02_Socket; PinSocket_1x02_P2.54mm_Vertical
K1, K2: SANYOU_SRD_Form_C; Relay_SPDT_SANYOU_SRD_Series_Form_C
Q1, Q2: BC337; TO-92_Inline
R1, R2: 1.8k; R_Axial_DIN0204_L3.6mm_D1.6mm_P7.62mm_Horizontal
R3, R4: 3.3k; R_Axial_DIN0204_L3.6mm_D1.6mm_P7.62mm_Horizontal
R5, R6: 47k; R_Axial_DIN0204_L3.6mm_D1.6mm_P7.62mm_Horizontal
SW1: SW_DIP_x01; PinHeader_1x02_P2.54mm_Vertical
U1: ESP32-DEVKIT-V1; ESP32_DEVKIT_V1; PARTREV N/A
U2: NRF24L01_Breakout; nRF24L01_Breakout

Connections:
3.3: J1.5, U1.1 (3V3), U2.2 (VCC)
CE: U1.5 (D4), U2.3 (CE)
CSN: U1.8 (D5), U2.4 (~CSN)
GND: GNDSCREW1.1, GNDSCREW2.1, GNDSCREW3.1, GNDSCREW4.1, J1.4, J2.2, J2.3, J3.2, J4.2, J5.2, Q1.3 (E), Q2.3 (E), R5.2, R6.2, U1.2 (GND), U1.29 (GND), U2.1 (GND)
IGN1: R3.1, U1.28 (D13)
IGN2: R4.1, U1.26 (D14)
IRQ: U1.4 (D2), U2.8 (IRQ)
MISO: U1.10 (D19), U2.7 (MISO)
MOSI: U1.15 (D23), U2.6 (MOSI)
unnamed: D1.2 (A), R1.1
unnamed: D1.1 (K), D4.2 (A), K1.2, Q1.1 (C)
unnamed: D2.2 (A), R2.1
unnamed: D2.1 (K), D3.2 (A), K2.2, Q2.1 (C)
unnamed: J2.1, SW1.1
unnamed: Q1.2 (B), R3.2, R5.1
unnamed: Q2.2 (B), R4.2, R6.1
P1: J3.1, K2.3
P2: J3.3, K1.3
RX: J1.2, U1.12 (RX0)
SCK: U1.9 (D18), U2.5 (SCK)
TX: J1.3, U1.13 (TX0)
VCC: J4.1, K1.1, K2.1, SW1.2, U1.30 (VIN)
VIN: D3.1 (K), D4.1 (K), J5.1, K1.5, K2.5, R1.2, R2.2

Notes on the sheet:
CONN- HC-12 RESPALDO

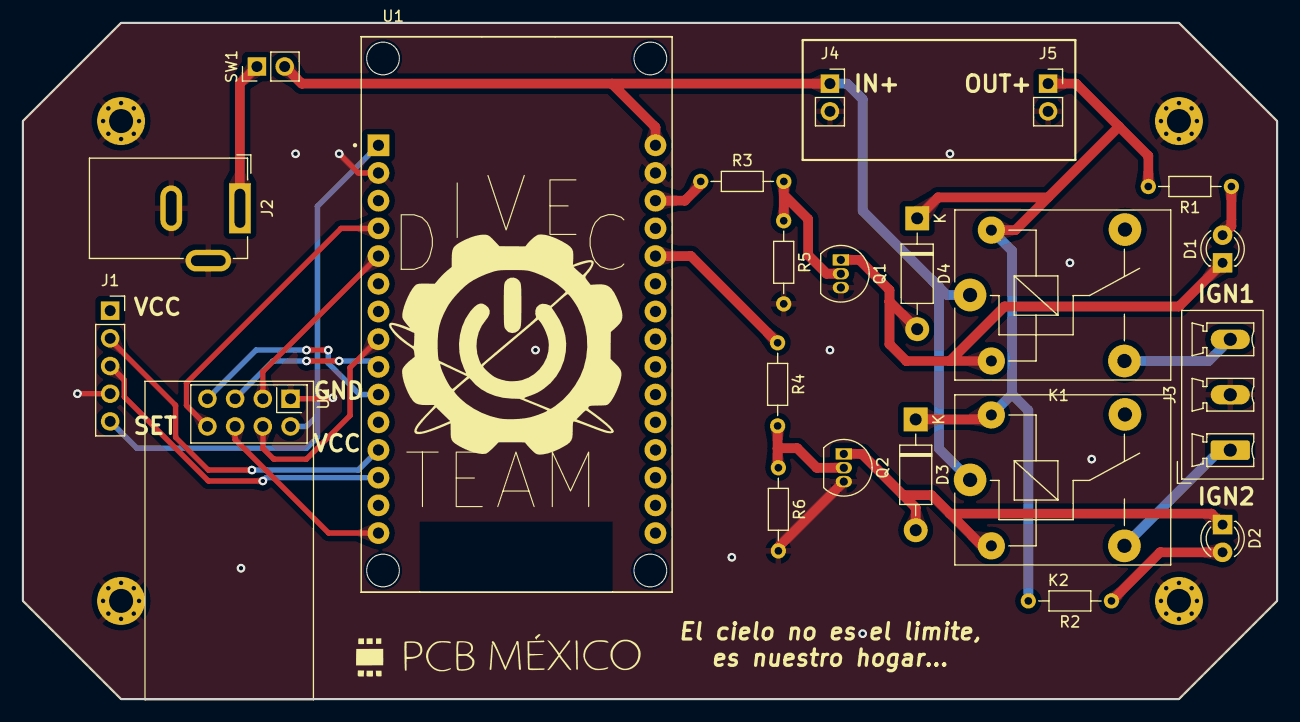
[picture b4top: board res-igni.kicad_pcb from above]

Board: 2 copper layers, 115.0 x 62.0 mm, 28 parts (1 on the bottom side), 23 nets.

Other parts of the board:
G1: LOGO; DIVEC_LOGO
G2: LOGO; SPACE
